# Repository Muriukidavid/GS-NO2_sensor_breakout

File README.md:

# GS-NO2_sensor_breakout
A breakout board to test GS+NO2 sensor

The sensor is a weak current source. This test circuit is a current to voltage converter with low power Opamps.

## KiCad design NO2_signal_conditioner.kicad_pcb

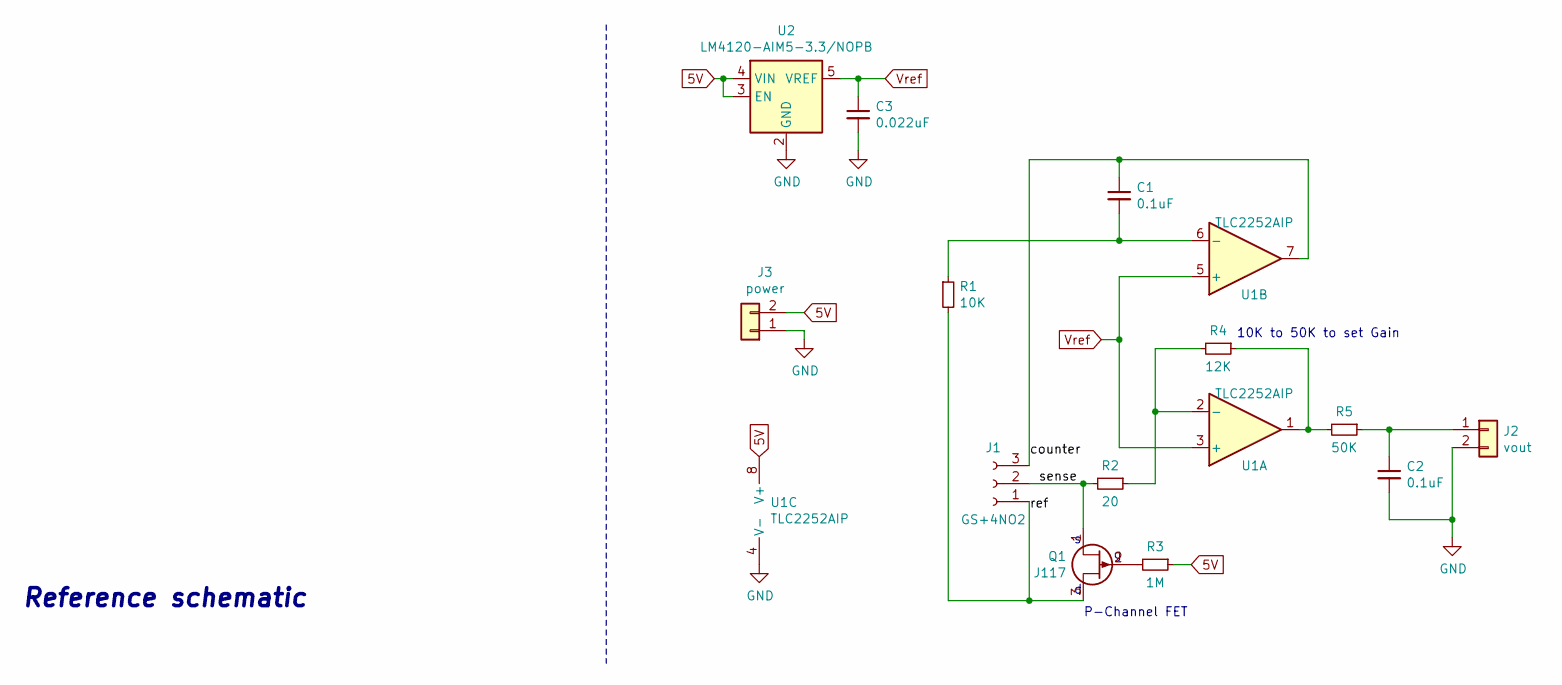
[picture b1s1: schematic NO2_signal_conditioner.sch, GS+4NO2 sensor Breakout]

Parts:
C1, C2: 0.1uF; C_0805_2012Metric; Mfr. # ECH-U1H101GB5
C3: 0.022uF; C_0805_2012Metric; Mfr. # 08055J220FBTTR
J1: GS+4NO2; TO-8-3_Window
J2: vout; PinHeader_1x02_P2.54mm_Vertical
J3: power; PinHeader_1x02_P2.54mm_Vertical
Q1: J117; SOT-23_Handsoldering; Mfr. # SSM3J117TU,LF
R1: 10K; R_0805_2012Metric; Mfr. # ERA-6AEB103V
R2: 20; R_0805_2012Metric; Mfr. # TNPW080520R0BEEN
R3: 1M; R_0805_2012Metric; Mfr. # ERA-6AEB105V
R4: 12K; R_0805_2012Metric; Mfr. # ERA-6AEB203V
R5: 50K; R_0805_2012Metric; Mfr. # PTN0805E5002BST1
U1: TLC2252AIP; DIP-8_W7.62mm; Mfr. # TLC2252AIP
U2: LM4120-AIM5-3.3/NOPB; SOT-23-5; Mfr. # LM4120AIM5-3.3/NOPB

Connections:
5V: J3.2, R3.1, U1.8 (V+), U2.3 (EN), U2.4 (VIN)
/counter: C1.1, J1.3, U1.7
/ref: J1.1, Q1.3 (S), R1.2
/sense: J1.2, Q1.1 (D), R2.2
GND: C2.2, C3.2, J2.2, J3.1, U1.4 (V-), U2.2 (GND)
unnamed: C1.2, R1.1, U1.6 (-)
unnamed: C2.1, J2.1, R5.1
unnamed: Q1.2 (G), R3.2
unnamed: R2.1, R4.2, U1.2 (-)
unnamed: R4.1, R5.2, U1.1
Vref: C3.1, U1.3 (+), U1.5 (+), U2.5 (VREF)

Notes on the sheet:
Reference schematic
10K to 50K to set Gain
P-Channel FET

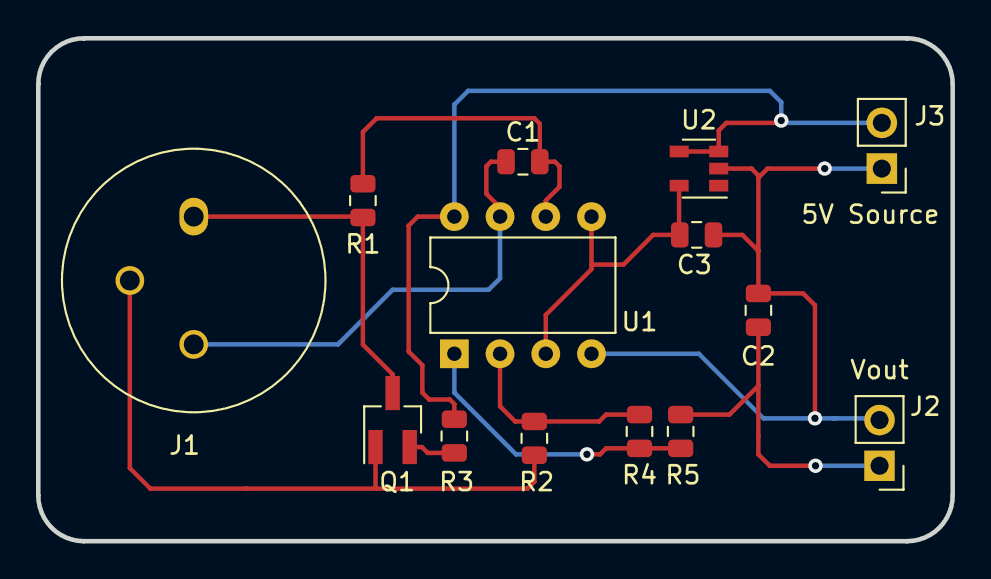
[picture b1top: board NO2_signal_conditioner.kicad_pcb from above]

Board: 2 copper layers, 50.8 x 27.9 mm, 14 parts (0 on the bottom side), 11 nets.

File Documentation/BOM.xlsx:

SN | Sourced | Placed | References | DKPN | Mfr. # | Value | Footprint | Quantity
1 | NO | NO | C3 | 478-11911-1-ND | 08055J220FBTTR | 0.022uF | C_0805_2012Metric | 1
2 | NO | NO | C1, C2 | PCF1089CT-ND | ECH-U1H101GB5 | 0.1uF | C_0805_2012Metric | 2
3 | NO | NO | R2 | 541-3759-1-ND | TNPW080520R0BEEN | 20Ohms | R_0805_2012Metric | 1
4 | NO | NO | R5 | 764-1535-1-ND | PTN0805E5002BST1 | 50K | R_0805_2012Metric | 1
5 | NO | NO | R1 | P10KDACT-ND | ERA-6AEB103V | 10K | R_0805_2012Metric | 1
6 | NO | NO | R3 | P1MDACT-ND | ERA-6AEB105V | 1M | R_0805_2012Metric | 1
7 | NO | NO | R4 | P20KDACT-ND | ERA-6AEB203V | 12K | R_0805_2012Metric | 1
8 | NO | NO | U1 | 296-7075-5-ND | TLC2252AIP | TLC272 | DIP-8_W7.62mm | 1
9 | NO | NO | U2 | LM4120AIM5-3.3/NOPBCT-ND | LM4120AIM5-3.3/NOPB | LM4120-AIMS-3.3/NOPB | SOT-23-5 | 1
10 | NO | NO | Q1 | SSM3J117TULFCT-ND | SSM3J117TU,LF | J117 | SOT-23_Handsoldering | 1
11 | NO | NO | J2 | vout | PinHeader_1x02_P2.54mm_Vertical | 1
12 | NO | NO | J3 | power | PinHeader_1x02_P2.54mm_Vertical | 1
13 | NO | NO | J1 | GS+4NO2 | TO-8-3_Window | 1

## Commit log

2020-11-27 Add initial revision of schematic, PCB layout, gerbers, SVG and a BOM
